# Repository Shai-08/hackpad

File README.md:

# hackpad

This is my (shrey's) hackpad

Features:

Case EC11 Rotary encoder for sound and volume (please double check if i did it right) 2 WS2812B RGB LEDs. 4 Keys

CAD Model:

This has 2 parts to the case, which will be held together with 4 M3 Screws

(I cant find a way to get a render without the lines, i tried rendering the image but the colors just aint it)

Schematic

Firmware:

This hackpad uses QMK firmware for everything.

The rotary encoder changes volume
The 4 keys currently act as macros

BOM:

4x Cherry MX Switches 
4x DSA Keycaps
4x M3x16mm SHCS Bolts 
2x WS2812B LEDs
1x EC11 Rotary Encoder
1x XIAO RP2040 
1x Case

video of everything working: https://youtu.be/ciVRcrCHMa8

finished product (the top part of the plate broke):

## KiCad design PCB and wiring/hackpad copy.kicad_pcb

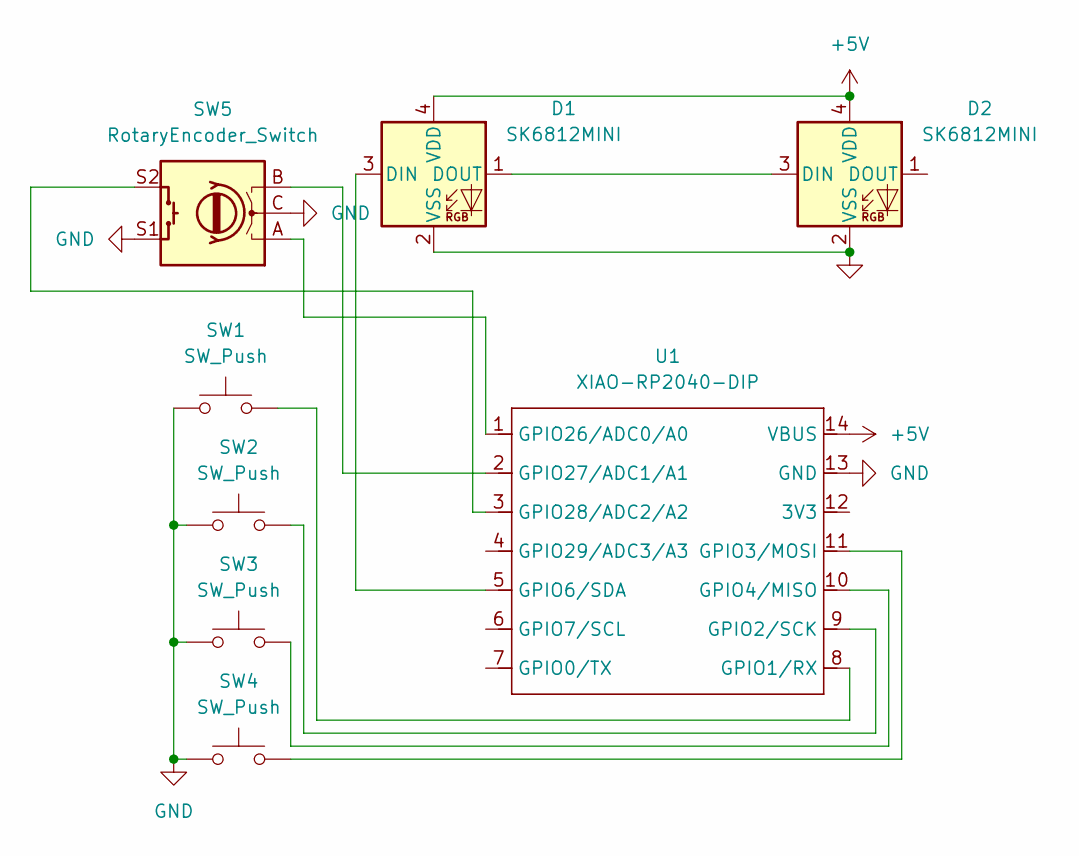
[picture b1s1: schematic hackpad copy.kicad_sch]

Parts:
D1, D2: SK6812MINI; LED_SK6812MINI_PLCC4_3.5x3.5mm_P1.75mm
SW1, SW2, SW3, SW4: SW_Push; SW_Cherry_MX_1.00u_PCB
SW5: RotaryEncoder_Switch; RotaryEncoder_Alps_EC11E-Switch_Vertical_H20mm
U1: XIAO-RP2040-DIP

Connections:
+5V: D1.4 (VDD), D2.4 (VDD), U1.14 (VBUS)
GND: D1.2 (VSS), D2.2 (VSS), SW1.1, SW2.1, SW3.1, SW4.1, SW5.C, SW5.S1, U1.13 (GND)
unnamed: D1.3 (DIN), U1.5 (GPIO6/SDA)
unnamed: D1.1 (DOUT), D2.3 (DIN)
unnamed: SW1.2, U1.8 (GPIO1/RX)
unnamed: SW2.2, U1.9 (GPIO2/SCK)
unnamed: SW4.2, U1.11 (GPIO3/MOSI)
unnamed: SW3.2, U1.10 (GPIO4/MISO)
unnamed: SW5.A, U1.1 (GPIO26/ADC0/A0)
unnamed: SW5.B, U1.2 (GPIO27/ADC1/A1)
unnamed: SW5.S2, U1.3 (GPIO28/ADC2/A2)

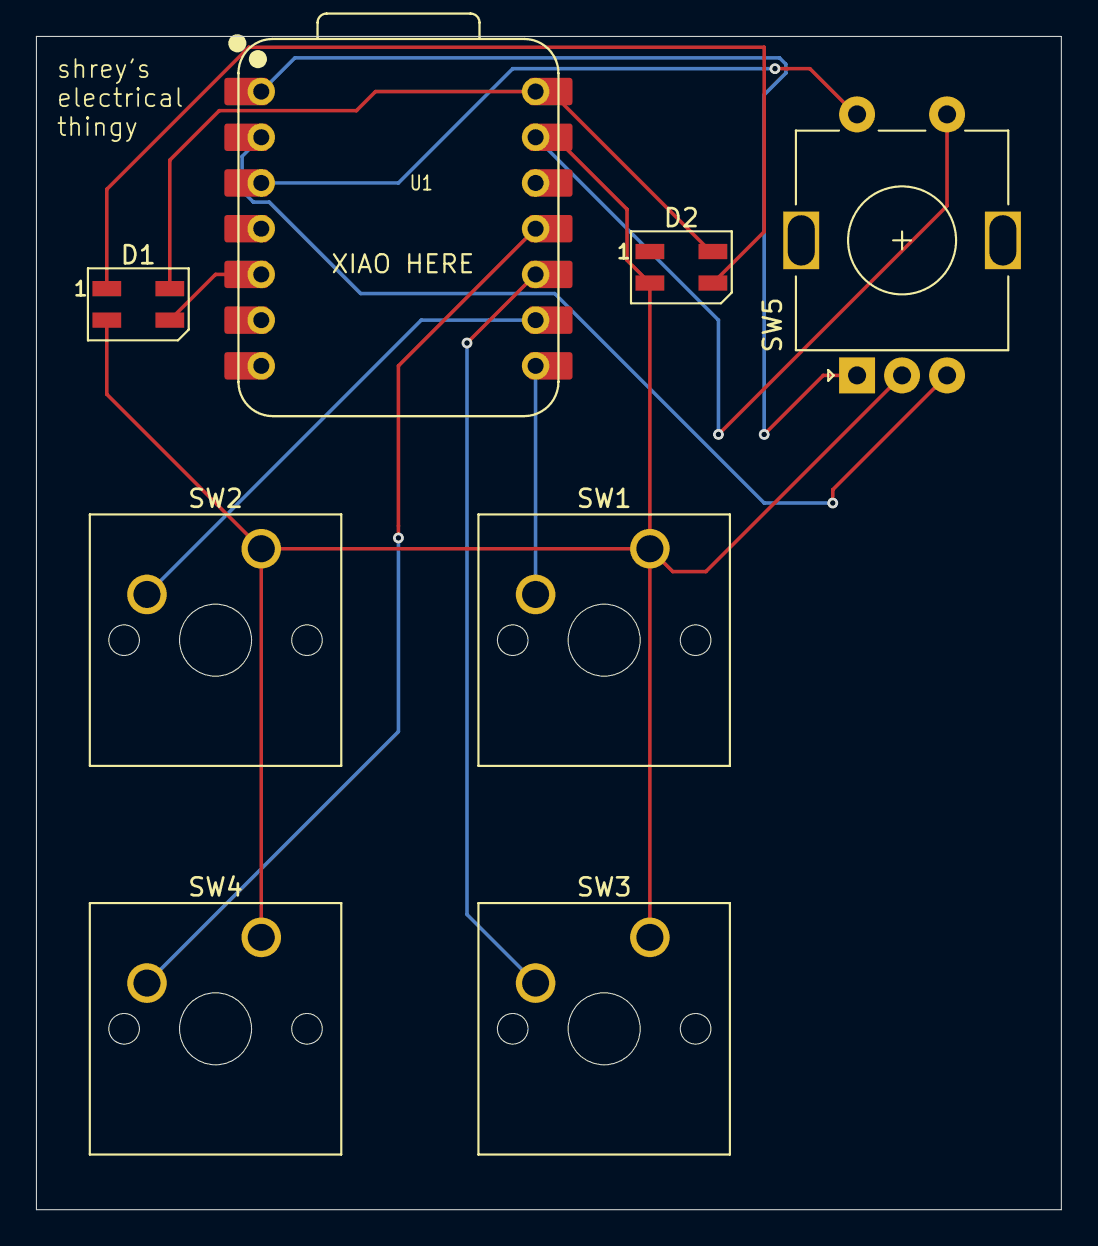
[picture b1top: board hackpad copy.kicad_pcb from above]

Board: 2 copper layers, 56.9 x 65.2 mm, 8 parts (0 on the bottom side), 11 nets.

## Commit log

2026-01-02 Add case image to README
    Added an image of the case to the README.
2026-01-02 Revise schematic section in README.md
    Updated schematic images and removed redundant text.
2026-01-02 Update PCB Schematic image link in README
2026-01-02 Revise README with firmware and BOM information
    Updated firmware overview and BOM details for clarity.
2026-01-02 Delete unnecessary caution from README
    Removed cautionary note about project uncertainty.
2026-01-03 Initialize firmware for keyboard with macros and encoder
2026-01-03 Fix image link syntax in README.md
2026-01-03 Fix image syntax in README.md
2026-01-03 Rename case.png to case1.png
2026-01-03 Replace case image and add additional images
    Updated case images and added a note about rendering issues.
2026-02-04 Rename IMG_1702.HEIC to completed.png
2026-02-06 Add image of finished product to README
2026-02-06 Update image link for finished product in README
2026-02-06 Update image link in README for finished product
